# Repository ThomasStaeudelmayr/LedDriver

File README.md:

This repository contains two distinct 4-channel LED driver hardware designs controlled by an **ESP32-S3 Zero**. Both versions support pulse-width modulation dimming.

- **Constant Current (CC) Driver:** Designed for high-power LEDs (like the Cree XLamp Color Series) that require current regulation.
    
- **Constant Voltage (CV) Driver:** Features 4 power MOSFETs designed for dimming standard 12V/24V RGBW LED strips.

## Hardware
### LED Driver CC

The CC version is built around the **LM3404** LED driver IC. This is a step-down switching regulator that drives the connected LEDs in constant current mode, eliminating the need for current-limiting resistors and increasing system efficiency.
#### Current Sense Resistor Calculation
The maximum forward current ($I_F$) delivered to the LEDs is determined by the value of the sense resistor ($R_{SNS}$) connected to the `CS` pin. Use the following formula to select your resistor value:

$$R_{SNS} = \frac{V_{REF}}{I_F} = \frac{0.2\text{ V}}{I_F}$$

Using a 0.2 $\Omega$ resistor sets the maximum forward current to 1.0 A.

#### Parts
| Part name                 | Quantity | Order number       | Distributor |
| ------------------------- | -------- | ------------------ | ---------- |
| ESP32-S3-Zero             | 1        | B0GV459V87         | Amazon     |
| LM3404                    | 4        | LM 3404 MA         | Reichelt   |
| DK_SLF10145 47uH          | 4        | 810-SLF10145T      | Mouser     |
| 0R2 2512                  | 4        | 708-RNCL2512FTR200 | Mouser     |
| SMAJ40A                   | 4        | 652-SMAJ40A        | Mouser     |
| DCDC Converter            | 1        | LME78_05-1.0       | Reichelt   |
| MCV_1,5_8-G-3.81          | 1        | 220-4888           | RS         |
| Fuse 5A                   | 1        | 576-0454005.NR     | Mouser     |
| MSTBVA 2-G 5,08           | 1        | STBVA 2-G 5,08     | Reichelt   |
| Capacitor 470uF 10x10 25V | 2        | -                  | -          |
| Capacitor 470nF 1210      | 4        | -                  | -          |
| Capacitor 2.2uF  1206     | 4        | -                  | -          |
| Capacitor 100nF 1206      | 8        | -                  | -          |
| Capacitor 10uF 1210       | 6        | -                  | -          |
| Resistor 500k 0805        | 4        | -                  | -          |

### LED Driver CV

The constant voltage version is designed for standard 12V/24V RGBW LED strips with integrated current-limiting resistors, utilizing 4 power MOSFETs as low-side switches. Dedicated gate drivers rapidly charge the MOSFET gate capacitance. The resulting fast rise and fall times minimize switching power losses during high-frequency PWM operation.
#### Parts
| Part name            | Quantity | Order number         | Distributor |
| -------------------- | -------- | -------------------- | ---------- |
| ESP32-S3-Zero        | 1        | B0GV459V87           | Amazon     |
| MCV_1,5_5-G-3.81     | 1        | 651-1803455          | Mouser     |
| MSTBVA 2-G 5,08      | 1        | STBVA 2-G 5,08       | Reichelt   |
| Capacitor 470uF      | 2        | FR-A 470U 63B        | Reichelt   |
| SMAJ40A              | 5        | 652-SMAJ40A          | Mouser     |
| Tantal 7343 100uF    | 2        | 80-T495D107M16ATE060 | Mouser     |
| 5V LDO               | 1        | 511-LD1117S50        | Mouser     |
| 9V DCDC Converter    | 1        | TSRN 1-2490          | Reichelt   |
| MCP1416 SOT-23-5     | 4        | 579-MCP1416RTEOTVAO  | Mouser     |
| Mosfet STD80N6F6     | 4        | 511-STD80N6F6        | Mouser     |
| Fuse 5A              | 1        | 576-0454005.NR     | Mouser     |
| Capacitor 10uF 1210  | 4        | -                    | -          |
| Capacitor 100nF 0805 | 4        | -                    | -          |
| Resistor 10R 0805    | 4        | -                    | -          |

## Software 

### ESP-NOW Control Example

The PC sends color values over a USB serial connection to the **Led Driver Bridge**, which then wirelessly sends those values to the **Led Driver Receiver**. 
#### 1. Get the Receiver's MAC Address
To pair the devices, you need the unique MAC address of the receiver board.
1. Upload the **Receiver Code** to your LED driver board.
2. Open the Serial Monitor. On startup, the ESP32 will print its MAC address.
3. Copy this address; you will need it for the transmitter code.
    
#### 2. Transmitter/Bridge Configuration & Operation
The transmitter connects to your PC via USB, listens for incoming serial data, and forwards it wirelessly.
1. Open the **Transmitter Code**.
2. Replace the placeholder bytes with your receiver's MAC address
3. Upload the code to the transmitter ESP32. 

```cpp
// Example: Replace with your actual receiver MAC address
uint8_t broadcastAddress[] = {0x34, 0xB7, 0xDA, 0x5B, 0x58, 0xE0};
```

#### Sending Control Commands 
The bridge ESP expects a single string formatted as `R:G:B:W` followed by a newline character (`\n`).  

**Example:** `1024:255:150:360` 

You can type this manually into the Arduino Serial Monitor or automate it using a program. This repository contains two python and one html example that generate the rgbw values. Once the transmitter gets a valid message, it splits the string into individual color values and sends them out over ESP-NOW. 

**LedDriver_web_app_rgbw.html** - control leds via a browser 
**LedDriver_control_hsv.py** - control leds via a python script 
**LedDriver_rgbw_waves.py** - python script that generates led animation 

#### How to execute Python Scripts 
1. In folder open CMD
2. generate environment (python -m venv env)
3. open environment via activate.bat
4. install modules using pip
5. execute 

### Web Server Example
The Web Server example eliminates the need for a dedicated transmitter controller. The ESP32 on the driver board will act as a web server. After altering the Wi-Fi name and password and uploading the code the leds can be controlled on: http://ledcontrol.local

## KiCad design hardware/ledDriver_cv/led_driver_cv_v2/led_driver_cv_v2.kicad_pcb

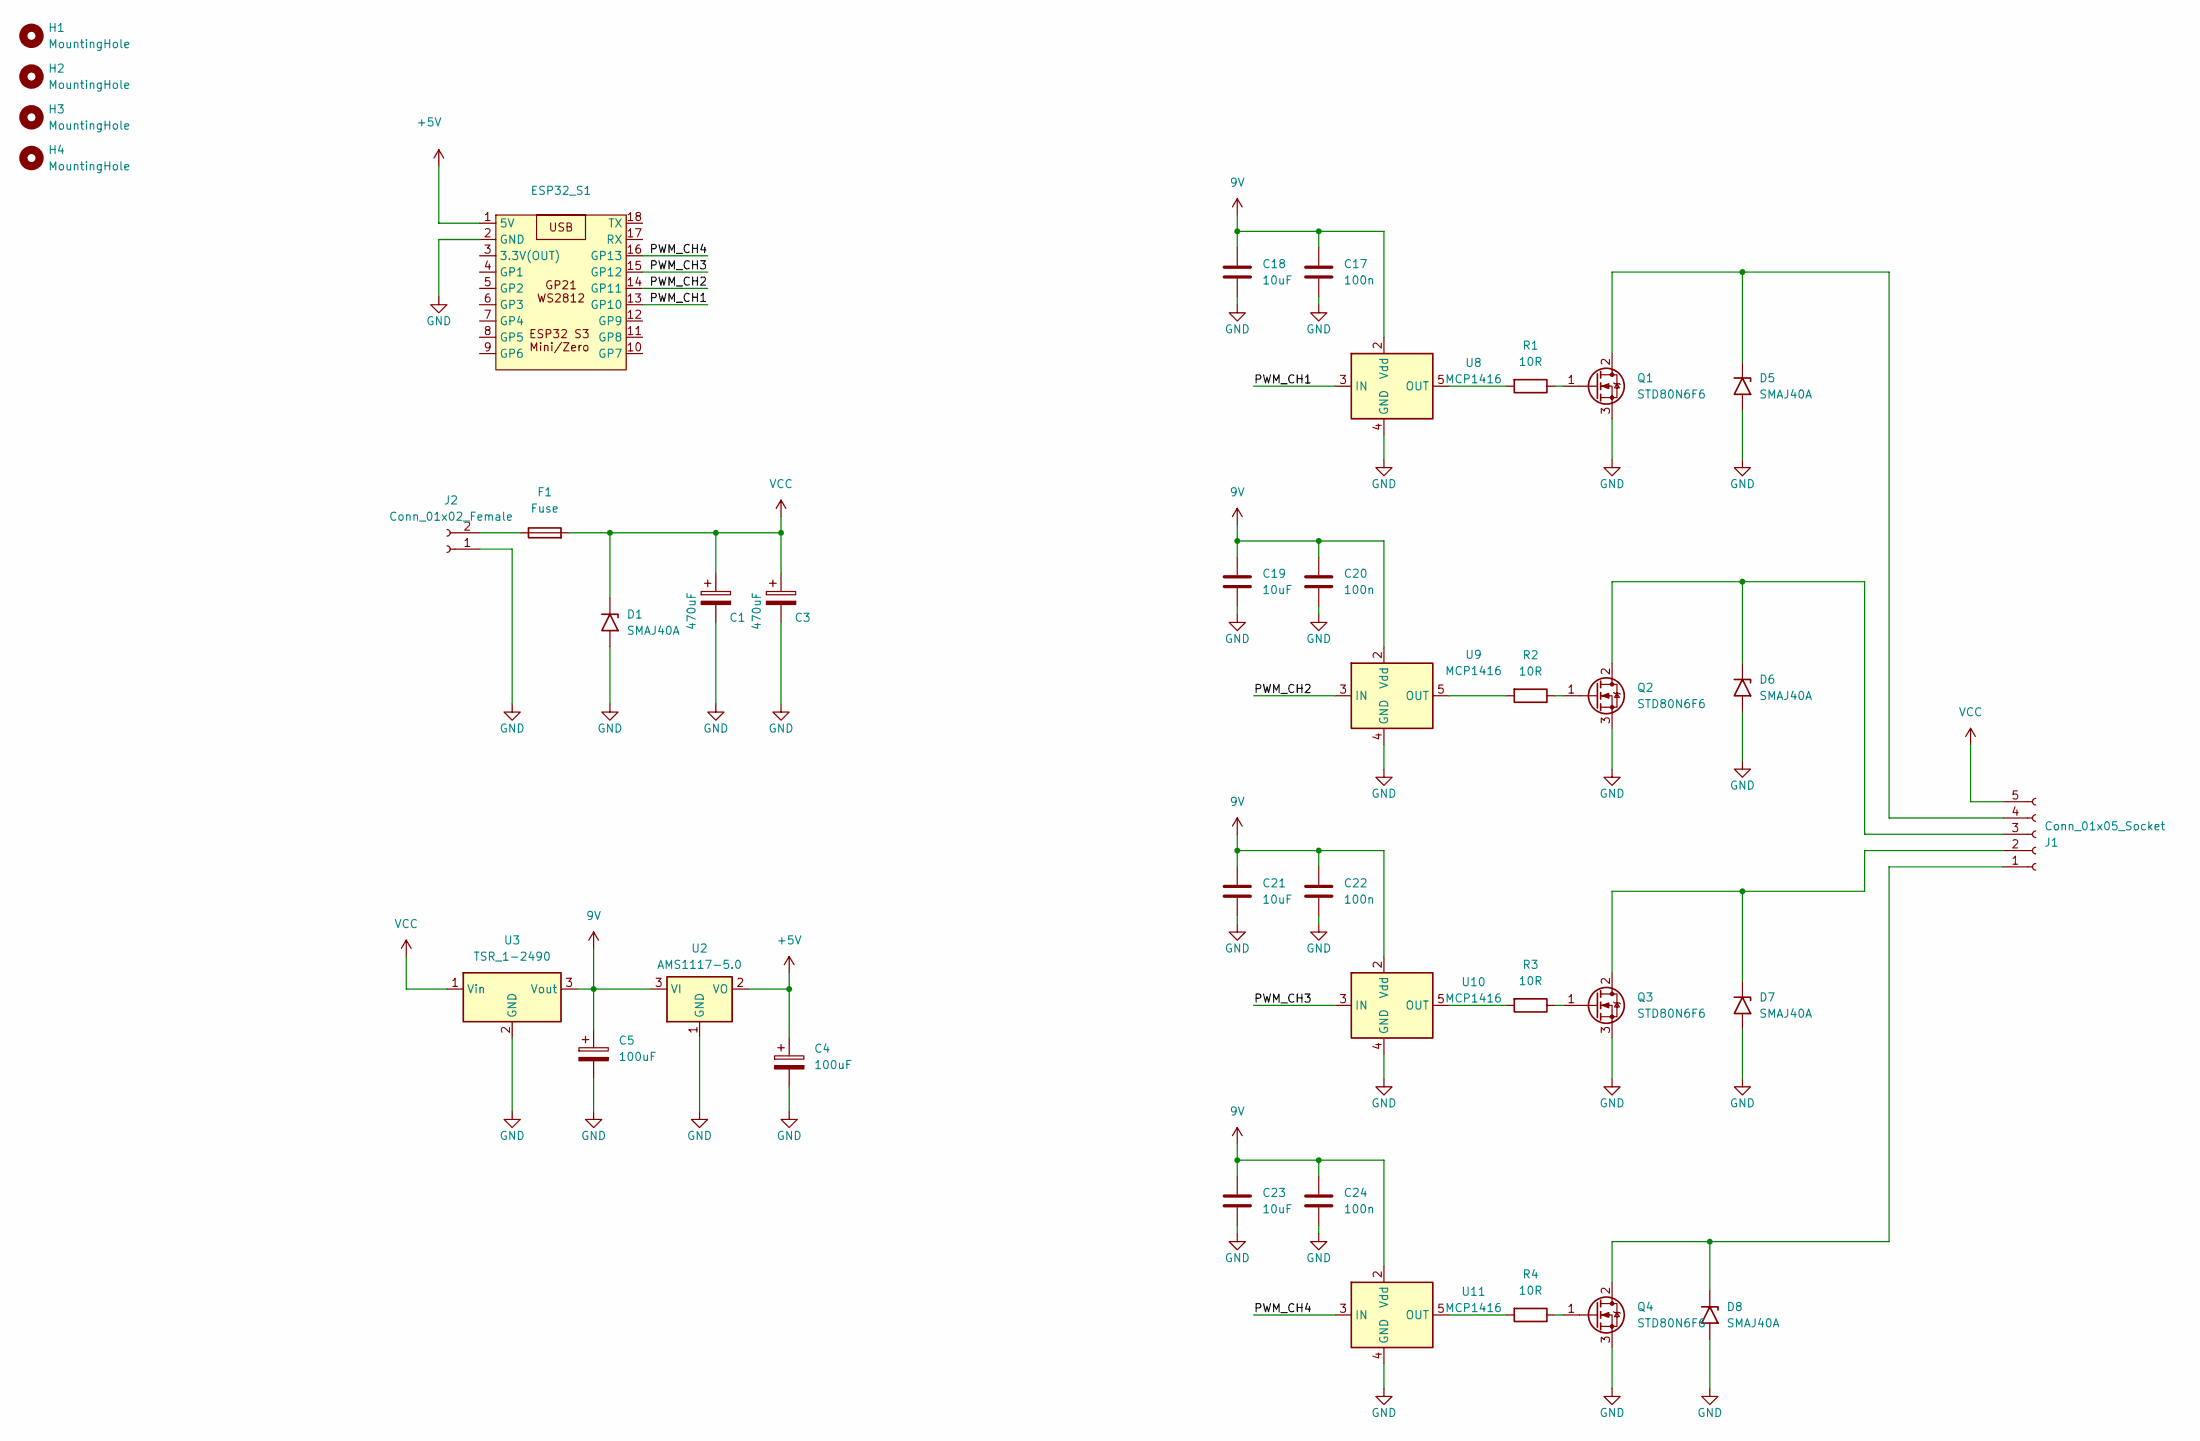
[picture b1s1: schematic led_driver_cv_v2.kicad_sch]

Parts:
C1, C3: 470uF; CP_Radial_D13.0mm_P5.00mm
C4, C5: 100uF; CP_EIA-7343-40_Kemet-Y_HandSolder
C17, C20, C22, C24: 100n; C_0805_2012Metric_Pad1.18x1.45mm_HandSolder
C18, C19, C21, C23: 10uF; C_1210_3225Metric_Pad1.33x2.70mm_HandSolder
D1, D5, D6, D7, D8: SMAJ40A; D_SMA
ESP32_S1: ESP32-S3-Zero
F1: Fuse; Fuse_Littelfuse-NANO2-451_453
H1: MountingHole; MountingHole_2.5mm
H2, H3, H4: MountingHole; MountingHole_3mm
J1: Conn_01x05_Socket; PhoenixContact_MCV_1,5_5-G-3.81_1x05_P3.81mm_Vertical
J2: Conn_01x02_Female; PhoenixContact_MSTBVA_2,5_2-G-5,08_1x02_P5.08mm_Vertical
Q1, Q2, Q3, Q4: STD80N6F6; TO-252-2
R1, R2, R3, R4: 10R; R_0805_2012Metric_Pad1.20x1.40mm_HandSolder
U2: AMS1117-5.0; SOT-223-3_TabPin2
U3: TSR_1-2490; Converter_DCDC_TRACO_TSR-1_THT
U8, U9, U10, U11: MCP1416; SOT-23-5

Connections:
9V: C5.1, C17.1, C18.1, C19.1, C20.1, C21.1, C22.1, C23.1, C24.1, U2.3 (VI), U3.3 (Vout), U8.2 (Vdd), U9.2 (Vdd), U10.2 (Vdd), U11.2 (Vdd)
+5V: C4.1, ESP32_S1.1 (5V), U2.2 (VO)
/PWM_CH1: ESP32_S1.13 (GP10), U8.3 (IN)
/PWM_CH2: ESP32_S1.14 (GP11), U9.3 (IN)
/PWM_CH3: ESP32_S1.15 (GP12), U10.3 (IN)
/PWM_CH4: ESP32_S1.16 (GP13), U11.3 (IN)
GND: C1.2, C3.2, C4.2, C5.2, C17.2, C18.2, C19.2, C20.2, C21.2, C22.2, C23.2, C24.2, D1.2 (A2), D5.2 (A2), D6.2 (A2), D7.2 (A2), D8.2 (A2), ESP32_S1.2 (GND), J2.1, Q1.3 (S), Q2.3 (S), Q3.3 (S), Q4.3 (S), U2.1 (GND), U3.2 (GND), U8.4 (GND), U9.4 (GND), U10.4 (GND), U11.4 (GND)
unnamed: D5.1 (A1), J1.4, Q1.2 (D)
unnamed: D6.1 (A1), J1.3, Q2.2 (D)
unnamed: D7.1 (A1), J1.2, Q3.2 (D)
unnamed: D8.1 (A1), J1.1, Q4.2 (D)
unnamed: F1.1, J2.2
unnamed: Q1.1 (G), R1.1
unnamed: Q2.1 (G), R2.1
unnamed: Q3.1 (G), R3.1
unnamed: Q4.1 (G), R4.1
unnamed: R1.2, U8.5 (OUT)
unnamed: R2.2, U9.5 (OUT)
unnamed: R3.2, U10.5 (OUT)
unnamed: R4.2, U11.5 (OUT)
VCC: C1.1, C3.1, D1.1 (A1), F1.2, J1.5, U3.1 (Vin)

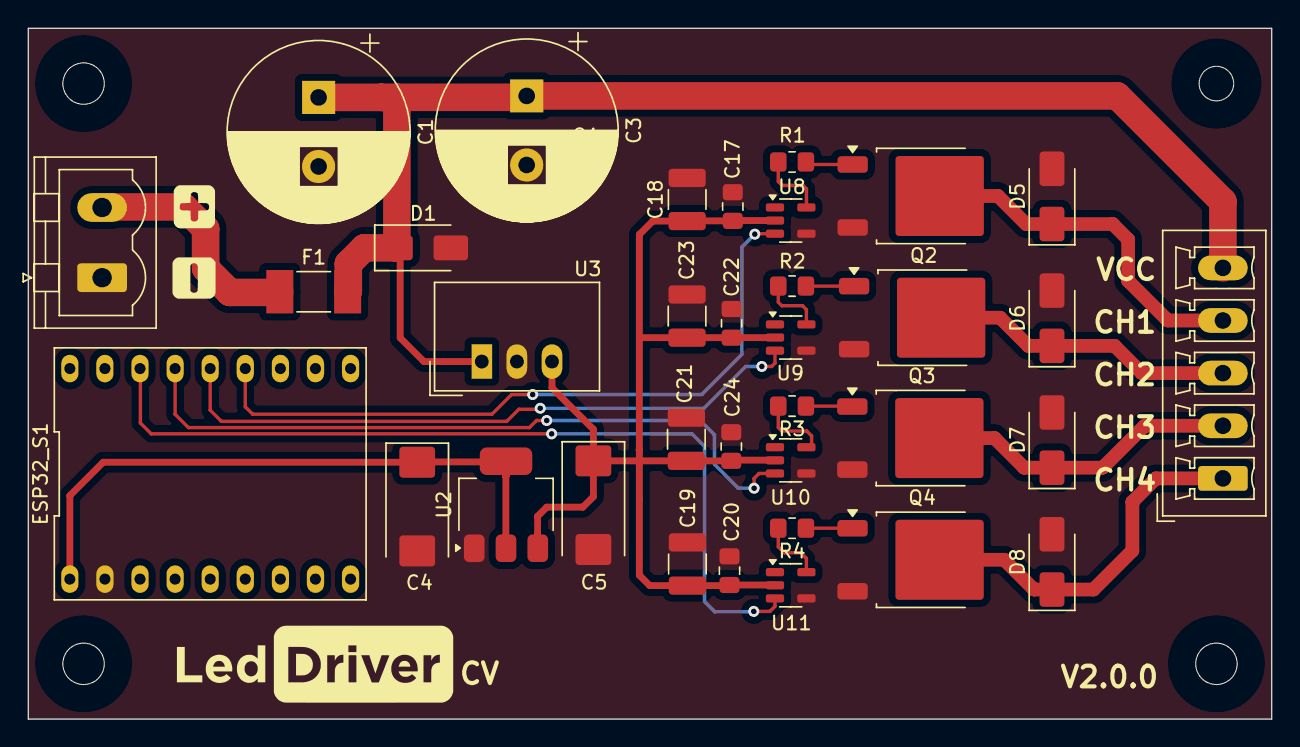
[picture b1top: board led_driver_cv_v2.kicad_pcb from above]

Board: 2 copper layers, 90.0 x 50.0 mm, 39 parts (0 on the bottom side), 21 nets.

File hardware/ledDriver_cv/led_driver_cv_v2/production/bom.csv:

Designator,Footprint,Quantity,Value,LCSC Part #
"C1, C3",CP_Radial_D13.0mm_P5.00mm,2,470uF,
"C17, C20, C22, C24",0805,4,100n,
"C18, C19, C21, C23",1210,4,10uF,
"C4, C5",CP_EIA-7343-40_Kemet-Y_HandSolder,2,100uF,
"D1, D5, D6, D7, D8",D_SMA,5,SMAJ40A,
ESP32_S1,ESP32-S3-Zero,1,~,
F1,Fuse_Littelfuse-NANO2-451_453,1,Fuse,
H1,MountingHole_2.5mm,1,MountingHole,
"H2, H3, H4",MountingHole_3mm,3,MountingHole,
J1,"PhoenixContact_MCV_1,5_5-G-3.81_1x05_P3.81mm_Vertical",1,Conn_01x05_Socket,
J2,"PhoenixContact_MSTBVA_2,5_2-G-5,08_1x02_P5.08mm_Vertical",1,Conn_01x02_Female,
"Q1, Q2, Q3, Q4",TO-252-2,4,QM6006D,
"R1, R2, R3, R4",0805,4,10R,
"U10, U11, U8, U9",SOT-23-5,4,MCP1416,
U2,SOT-223-3_TabPin2,1,AMS1117-5.0,
U3,Converter_DCDC_TRACO_TSR-1_THT,1,TSR_1-2490,

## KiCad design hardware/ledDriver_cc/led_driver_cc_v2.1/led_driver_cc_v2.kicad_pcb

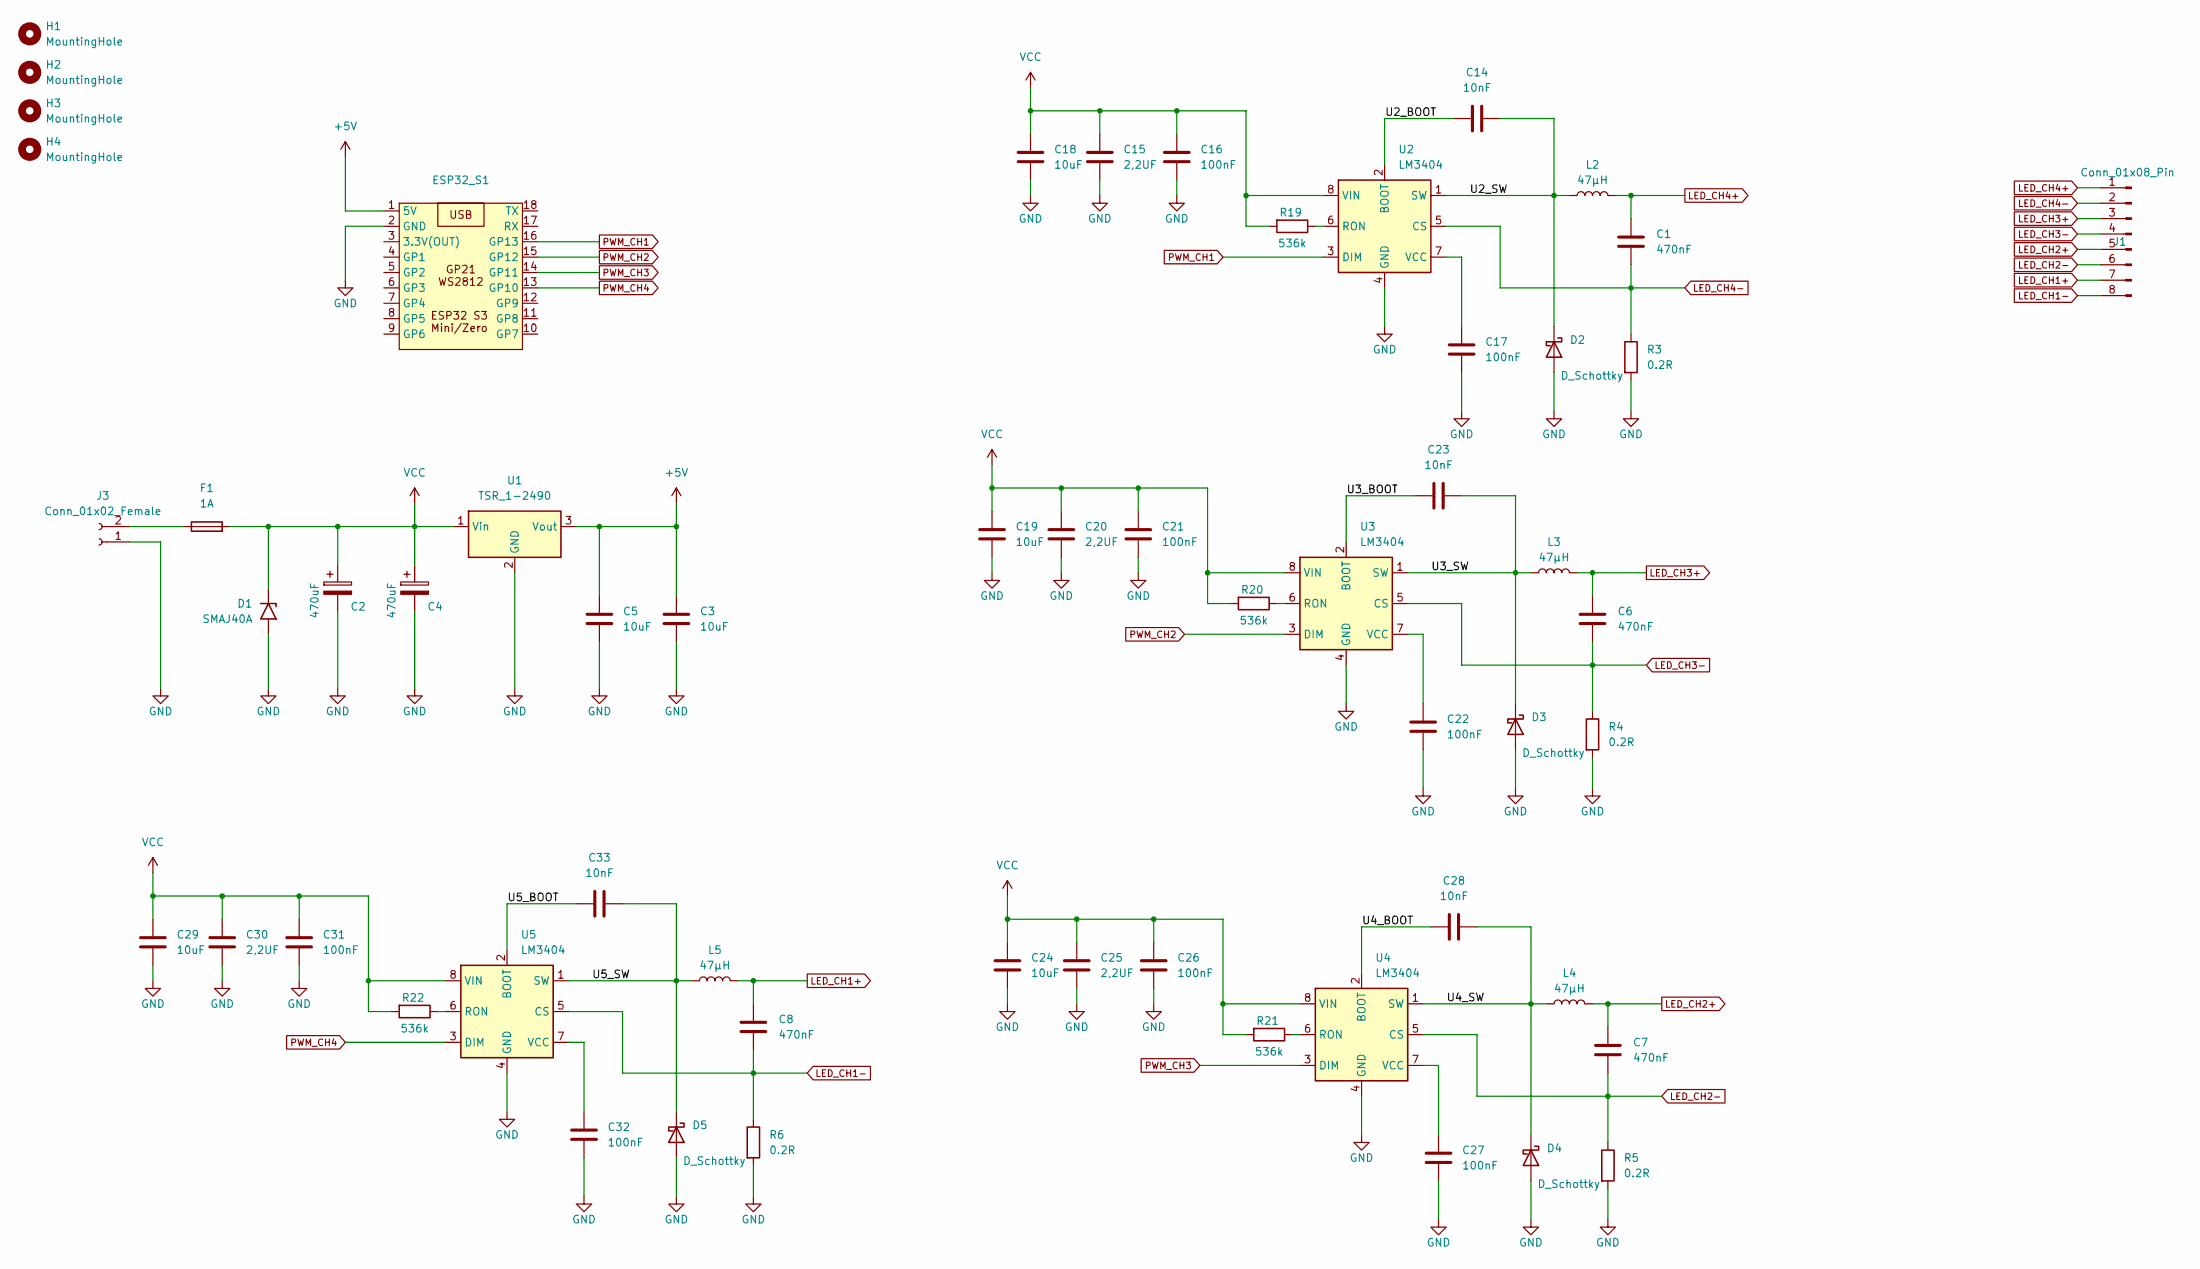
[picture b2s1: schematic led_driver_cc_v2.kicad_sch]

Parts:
C1, C6, C7, C8: 470nF; C_1210_3225Metric_Pad1.33x2.70mm_HandSolder
C2, C4: 470uF; CP_Elec_10x10
C3, C5, C18, C19, C24, C29: 10uF; C_1210_3225Metric_Pad1.33x2.70mm_HandSolder
C14, C23, C28, C33: 10nF; C_1206_3216Metric_Pad1.33x1.80mm_HandSolder
C15, C20, C25, C30: 2,2UF; C_1206_3216Metric_Pad1.33x1.80mm_HandSolder
C16, C17, C21, C22, C26, C27, C31, C32: 100nF; C_1206_3216Metric_Pad1.33x1.80mm_HandSolder
D1: SMAJ40A; D_SMA
D2, D3, D4, D5: D_Schottky; D_SMB
ESP32_S1: ESP32-S3-Zero
F1: 1A; Fuse_Littelfuse-NANO2-451_453
H1, H2, H3, H4: MountingHole; MountingHole_3.2mm_M3
J1: Conn_01x08_Pin; PhoenixContact_MCV_1,5_8-G-3.81_1x08_P3.81mm_Vertical
J3: Conn_01x02_Female; PhoenixContact_MSTBVA_2,5_2-G_1x02_P5.00mm_Vertical
L2, L3, L4, L5: 47µH; L_TDK_SLF10145
R3, R4, R5, R6: 0.2R; R_2512_6332Metric_Pad1.40x3.35mm_HandSolder
R19, R20, R21, R22: 536k; R_0805_2012Metric_Pad1.20x1.40mm_HandSolder
U1: TSR_1-2490; Converter_DCDC_TRACO_TSR-1_THT
U2, U3, U4, U5: LM3404; SOIC-8_3.9x4.9mm_P1.27mm

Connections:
+5V: C3.1, C5.1, ESP32_S1.1 (5V), U1.3 (Vout)
/U2_BOOT: C14.1, U2.2 (BOOT)
/U2_SW: C14.2, D2.1 (K), L2.1, U2.1 (SW)
/U3_BOOT: C23.1, U3.2 (BOOT)
/U3_SW: C23.2, D3.1 (K), L3.1, U3.1 (SW)
/U4_BOOT: C28.1, U4.2 (BOOT)
/U4_SW: C28.2, D4.1 (K), L4.1, U4.1 (SW)
/U5_BOOT: C33.1, U5.2 (BOOT)
/U5_SW: C33.2, D5.1 (K), L5.1, U5.1 (SW)
GND: C2.2, C3.2, C4.2, C5.2, C15.1, C16.1, C17.1, C18.1, C19.1, C20.1, C21.1, C22.1, C24.1, C25.1, C26.1, C27.1, C29.1, C30.1, C31.1, C32.1, D1.2 (A2), D2.2 (A), D3.2 (A), D4.2 (A), D5.2 (A), ESP32_S1.2 (GND), J3.1, R3.2, R4.2, R5.2, R6.2, U1.2 (GND), U2.4 (GND), U3.4 (GND), U4.4 (GND), U5.4 (GND)
LED_CH1+: C8.1, J1.7, L5.2
LED_CH1-: C8.2, J1.8, R6.1, U5.5 (CS)
LED_CH2+: C7.1, J1.5, L4.2
LED_CH2-: C7.2, J1.6, R5.1, U4.5 (CS)
LED_CH3+: C6.1, J1.3, L3.2
LED_CH3-: C6.2, J1.4, R4.1, U3.5 (CS)
LED_CH4+: C1.1, J1.1, L2.2
LED_CH4-: C1.2, J1.2, R3.1, U2.5 (CS)
unnamed: F1.1, J3.2
unnamed: R19.1, U2.6 (RON)
unnamed: C17.2, U2.7 (VCC)
unnamed: R20.1, U3.6 (RON)
unnamed: C22.2, U3.7 (VCC)
unnamed: R21.1, U4.6 (RON)
unnamed: C27.2, U4.7 (VCC)
unnamed: R22.1, U5.6 (RON)
unnamed: C32.2, U5.7 (VCC)
PWM_CH1: ESP32_S1.16 (GP13), U2.3 (DIM)
PWM_CH2: ESP32_S1.15 (GP12), U3.3 (DIM)
PWM_CH3: ESP32_S1.14 (GP11), U4.3 (DIM)
PWM_CH4: ESP32_S1.13 (GP10), U5.3 (DIM)
VCC: C2.1, C4.1, C15.2, C16.2, C18.2, C19.2, C20.2, C21.2, C24.2, C25.2, C26.2, C29.2, C30.2, C31.2, D1.1 (A1), F1.2, R19.2, R20.2, R21.2, R22.2, U1.1 (Vin), U2.8 (VIN), U3.8 (VIN), U4.8 (VIN), U5.8 (VIN)

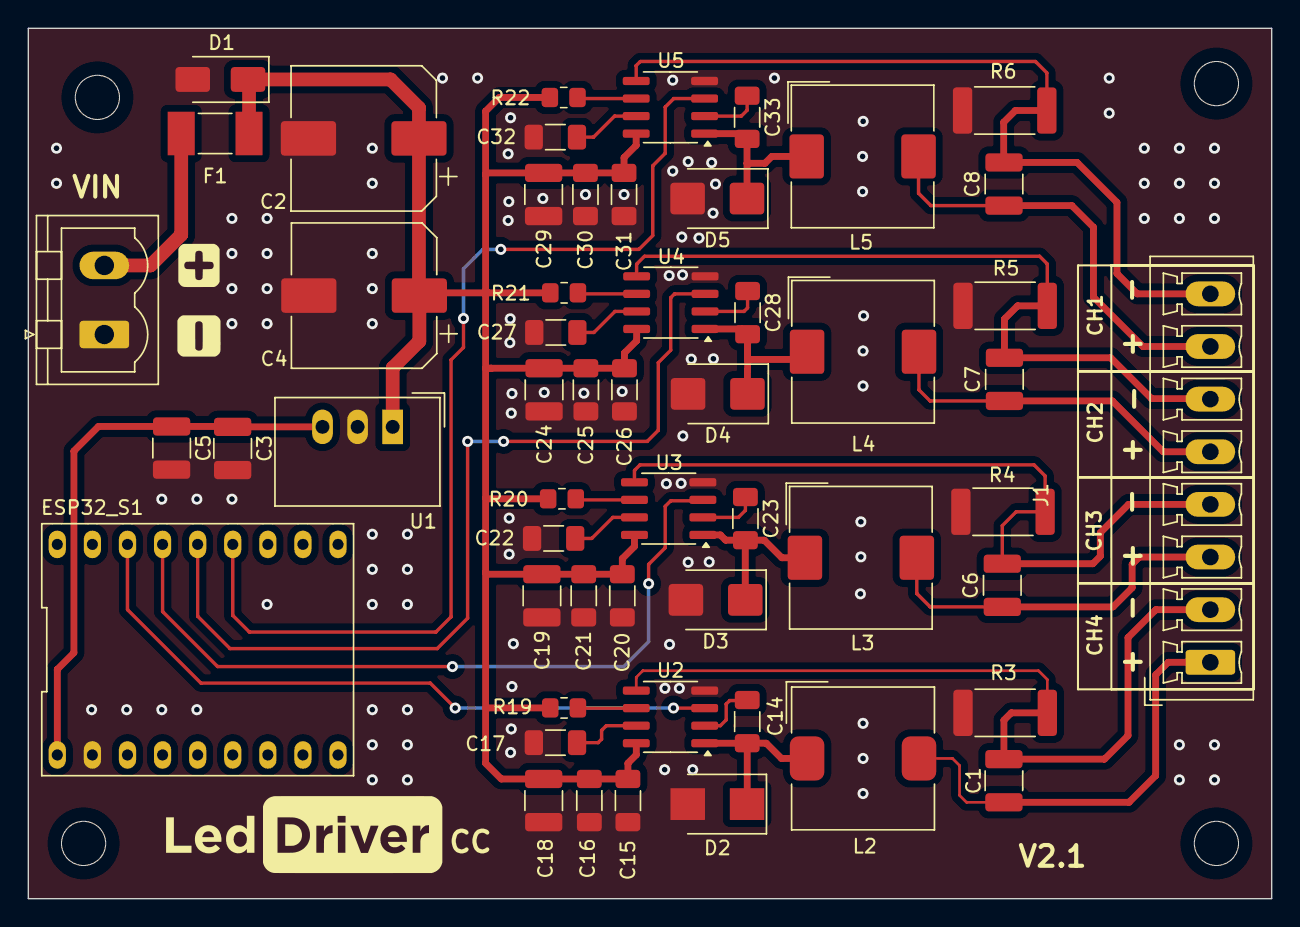
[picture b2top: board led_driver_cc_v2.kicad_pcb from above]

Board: 2 copper layers, 90.0 x 63.0 mm, 58 parts (0 on the bottom side), 32 nets.

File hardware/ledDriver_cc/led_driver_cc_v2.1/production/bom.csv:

Designator,Footprint,Quantity,Value,LCSC Part #
"C1, C6, C7, C8",1210,4,470nF,
"C14, C23, C28, C33",1206,4,10nF,
"C15, C20, C25, C30",1206,4,"2,2UF",
"C16, C17, C21, C22, C26, C27, C31, C32",1206,8,100nF,
"C18, C19, C24, C29, C3, C5",1210,6,10uF,
"C2, C4",CP_Elec_10x10,2,470uF,
D1,D_SMA,1,SMAJ40A,
"D2, D3, D4, D5",D_SMB,4,D_Schottky,
ESP32_S1,ESP32-S3-Zero,1,~,
F1,Fuse_Littelfuse-NANO2-451_453,1,1A,
"H1, H2, H3, H4",MountingHole_3.2mm_M3,4,MountingHole,
J1,"PhoenixContact_MCV_1,5_8-G-3.81_1x08_P3.81mm_Vertical",1,Conn_01x08_Pin,
J3,"PhoenixContact_MSTBVA_2,5_2-G_1x02_P5.00mm_Vertical",1,Conn_01x02_Female,
"L2, L3, L4, L5",L_TDK_SLF10145,4,47µH,
"R19, R20, R21, R22",0805,4,536k,
"R3, R4, R5, R6",2512,4,0.2R,
U1,Converter_DCDC_TRACO_TSR-1_THT,1,TSR_1-2490,
"U2, U3, U4, U5",SOIC-8_3.9x4.9mm_P1.27mm,4,LM3404,

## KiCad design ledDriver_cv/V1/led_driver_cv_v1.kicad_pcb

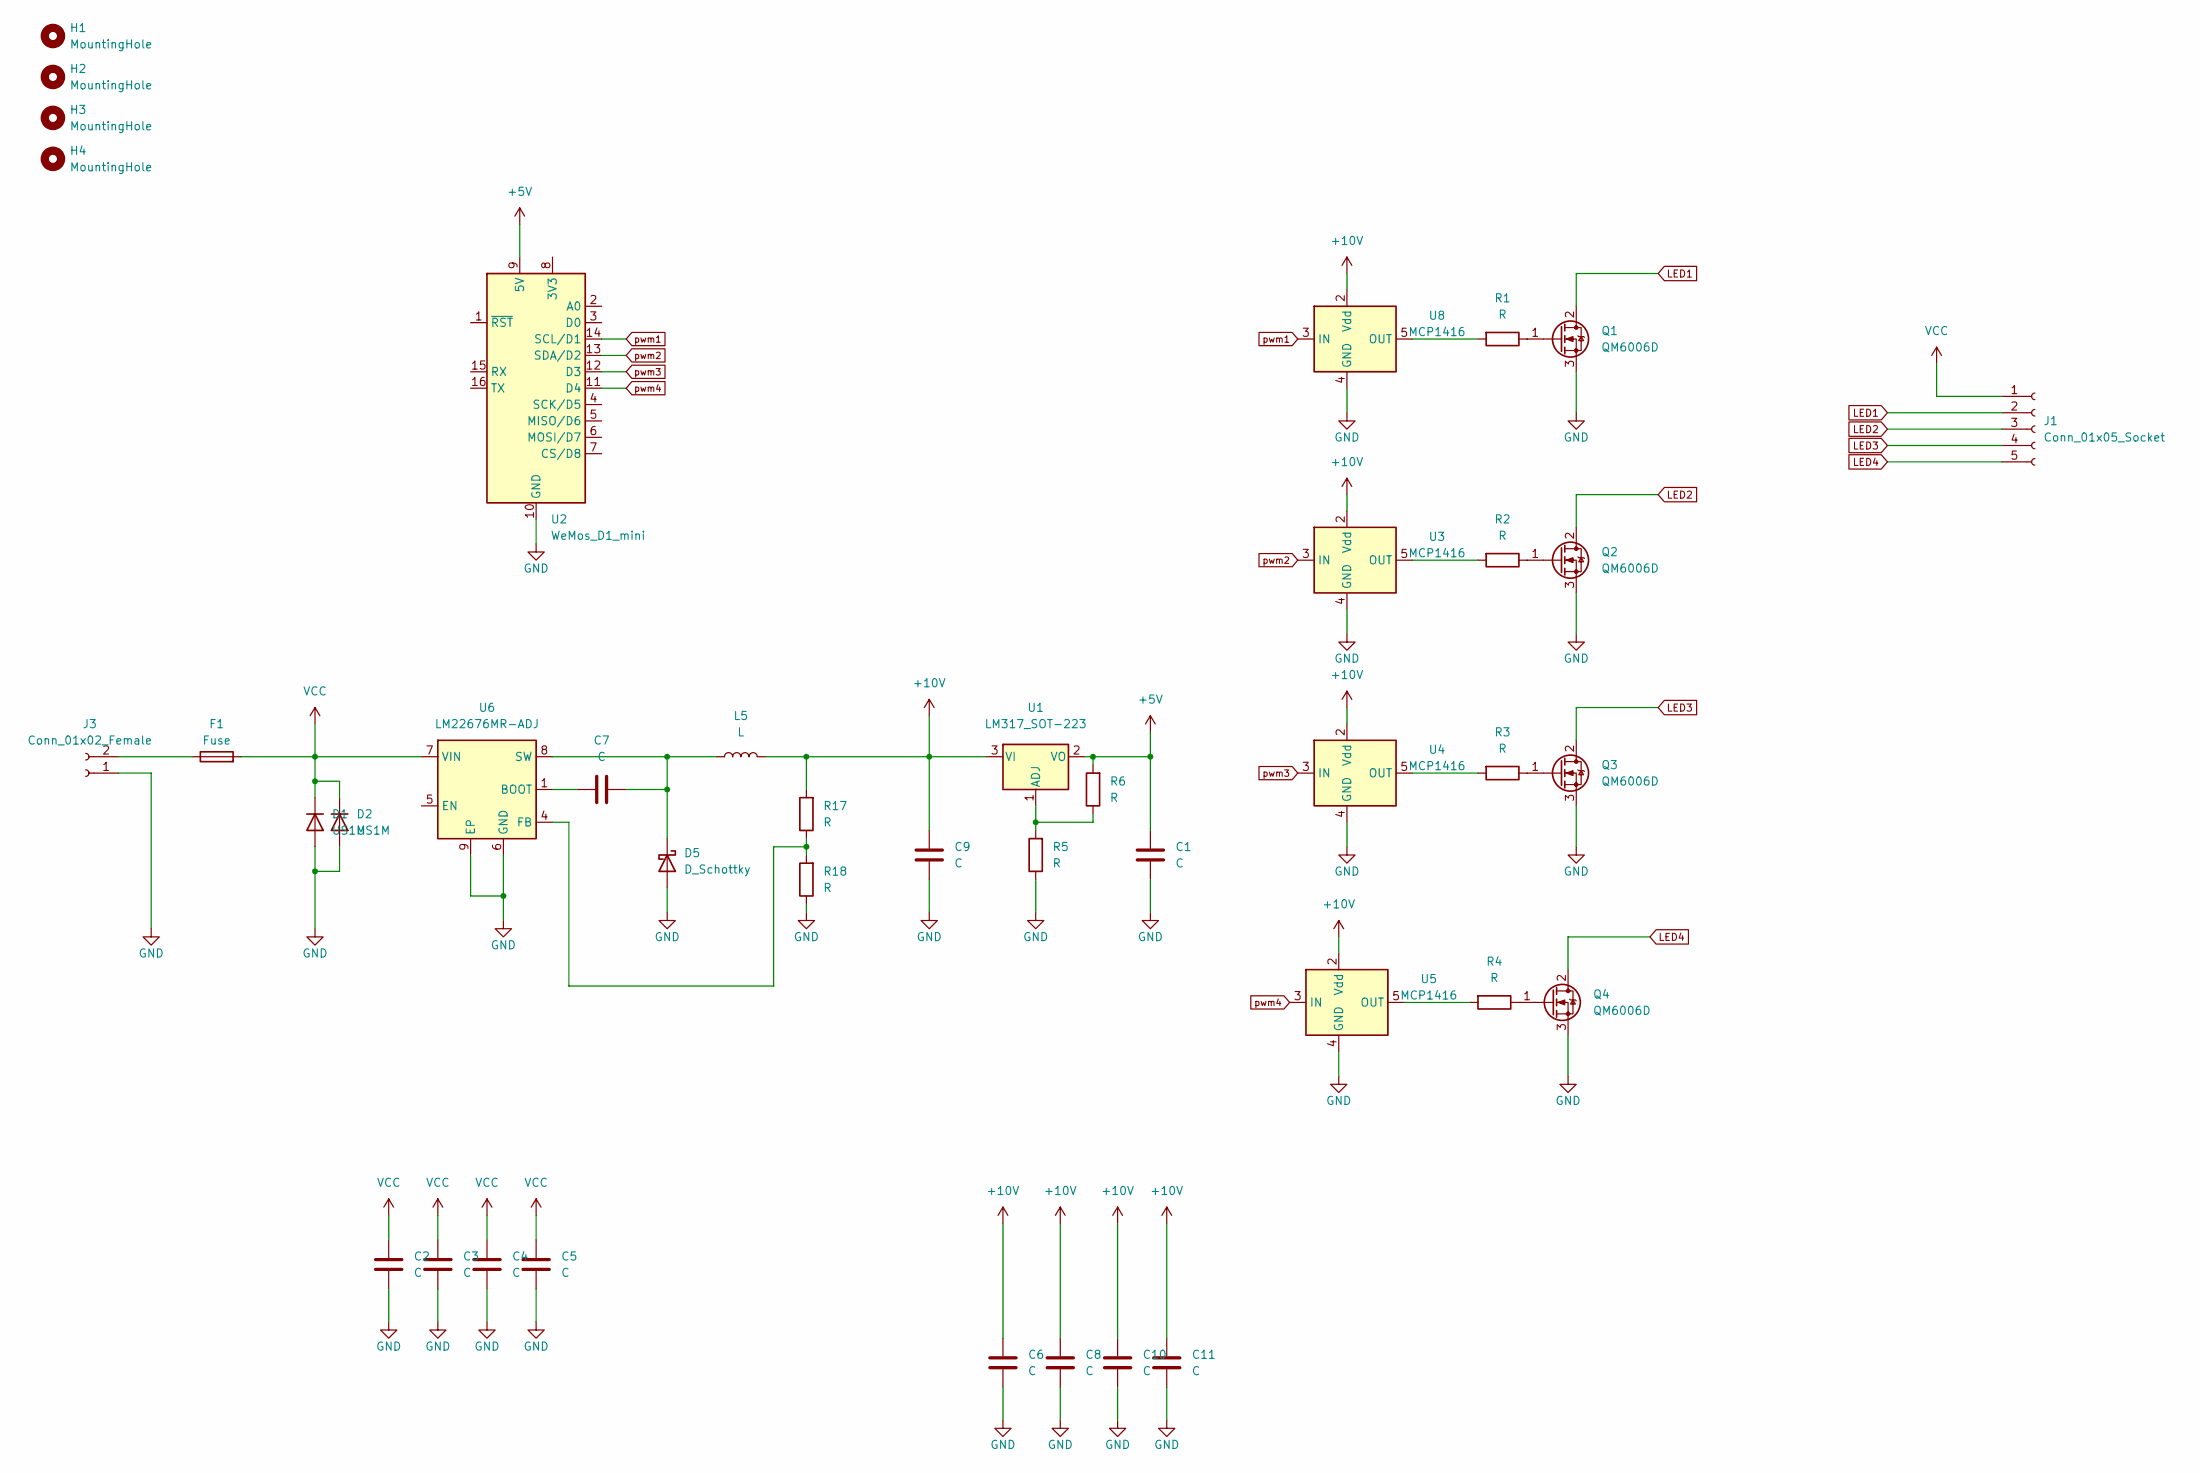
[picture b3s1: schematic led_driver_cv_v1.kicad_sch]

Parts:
C1, C2, C3, C4, C5, C9: C; C_1210_3225Metric_Pad1.33x2.70mm_HandSolder
C6, C8, C10, C11: C; L_1206_3216Metric
C7: C; C_1206_3216Metric_Pad1.33x1.80mm_HandSolder
D1, D2: US1M; D_SMA
D5: D_Schottky; D_SMB
F1: Fuse; Fuse_2512_6332Metric
H1, H2, H3, H4: MountingHole; MountingHole_2.5mm
J1: Conn_01x05_Socket; PhoenixContact_MSTBVA_2,5_5-G-5,08_1x05_P5.08mm_Vertical
J3: Conn_01x02_Female; PhoenixContact_MSTBVA_2,5_2-G_1x02_P5.00mm_Vertical
L5: L; L_10.4x10.4_H4.8
Q1, Q2, Q3, Q4: QM6006D; TO-252-2
R1, R2, R3, R4, R5, R6, R17, R18: R; R_1206_3216Metric
U1: LM317_SOT-223; SOT-223-3_TabPin2
U2: WeMos_D1_mini; WEMOS_D1_mini_light
U3, U4, U5, U8: MCP1416; SOT-23-5
U6: LM22676MR-ADJ; TI_SO-PowerPAD-8

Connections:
+5V: C1.1, R6.2, U1.2 (VO), U2.9 (5V)
+10V: C6.1, C8.1, C9.1, C10.1, C11.1, L5.2, R17.2, U1.3 (VI), U3.2 (Vdd), U4.2 (Vdd), U5.2 (Vdd), U8.2 (Vdd)
GND: C1.2, C2.2, C3.2, C4.2, C5.2, C6.2, C8.2, C9.2, C10.2, C11.2, D1.2 (A), D2.2 (A), D5.2 (A), J3.1, Q1.3 (S), Q2.3 (S), Q3.3 (S), Q4.3 (S), R5.1, R18.1, U2.10 (GND), U3.4 (GND), U4.4 (GND), U5.4 (GND), U6.6 (GND), U6.9 (EP), U8.4 (GND)
LED1: J1.2, Q1.2 (D)
LED2: J1.3, Q2.2 (D)
LED3: J1.4, Q3.2 (D)
LED4: J1.5, Q4.2 (D)
unnamed: C7.2, D5.1 (K), L5.1, U6.8 (SW)
unnamed: F1.1, J3.2
unnamed: Q1.1 (G), R1.1
unnamed: Q2.1 (G), R2.1
unnamed: Q3.1 (G), R3.1
unnamed: Q4.1 (G), R4.1
unnamed: R5.2, R6.1, U1.1 (ADJ)
unnamed: R2.2, U3.5 (OUT)
unnamed: R3.2, U4.5 (OUT)
unnamed: R4.2, U5.5 (OUT)
unnamed: C7.1, U6.1 (BOOT)
unnamed: R17.1, R18.2, U6.4 (FB)
unnamed: R1.2, U8.5 (OUT)
VCC: C2.1, C3.1, C4.1, C5.1, D1.1 (K), D2.1 (K), F1.2, J1.1, U6.7 (VIN)
pwm1: U2.14 (SCL/D1), U8.3 (IN)
pwm2: U2.13 (SDA/D2), U3.3 (IN)
pwm3: U2.12 (D3), U4.3 (IN)
pwm4: U2.11 (D4), U5.3 (IN)

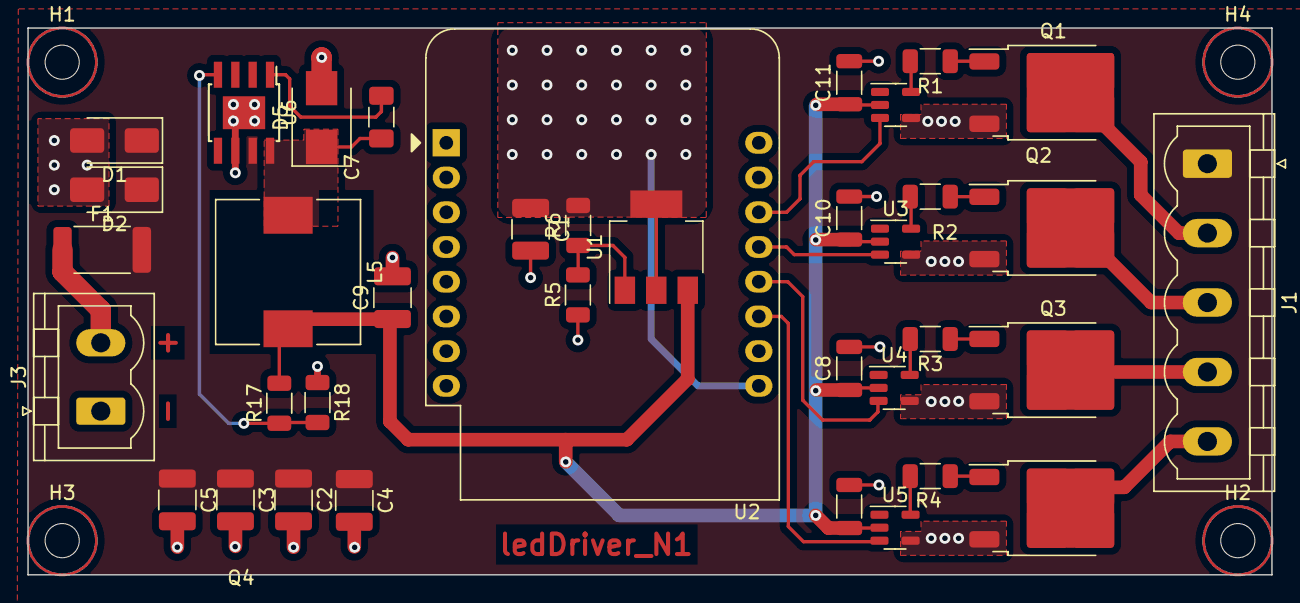
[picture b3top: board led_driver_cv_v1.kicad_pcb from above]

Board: 2 copper layers, 91.0 x 40.0 mm, 41 parts (0 on the bottom side), 25 nets.
